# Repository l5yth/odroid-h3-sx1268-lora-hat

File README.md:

# odroid-h3-sx1268-lora-hat

Kicad files for an ODROID H3/H3+ to Raspberry-Pi pin header translator to be used with the Waveshare SX1268 LoRa hat.

* Discussion: [forum.odroid.com/topic/50464](https://forum.odroid.com/viewtopic.php?f=171&t=50464&p=400427)
* Waveshare SX1268 LoRa schematics: [files.waveshare.com/SX1268_LoRa_HAT_SchDoc.pdf](https://files.waveshare.com/upload/a/af/SX1268_LoRa_HAT_SchDoc.pdf)
* ODROID H3 schematics: [wiki.odroid.com/odroid-h3/odroid-h3_rev2.0_20220406.pdf](https://wiki.odroid.com/_media/odroid-h3/odroid-h3_rev2.0_20220406.pdf)

## LICENSE

CC0 - public domain

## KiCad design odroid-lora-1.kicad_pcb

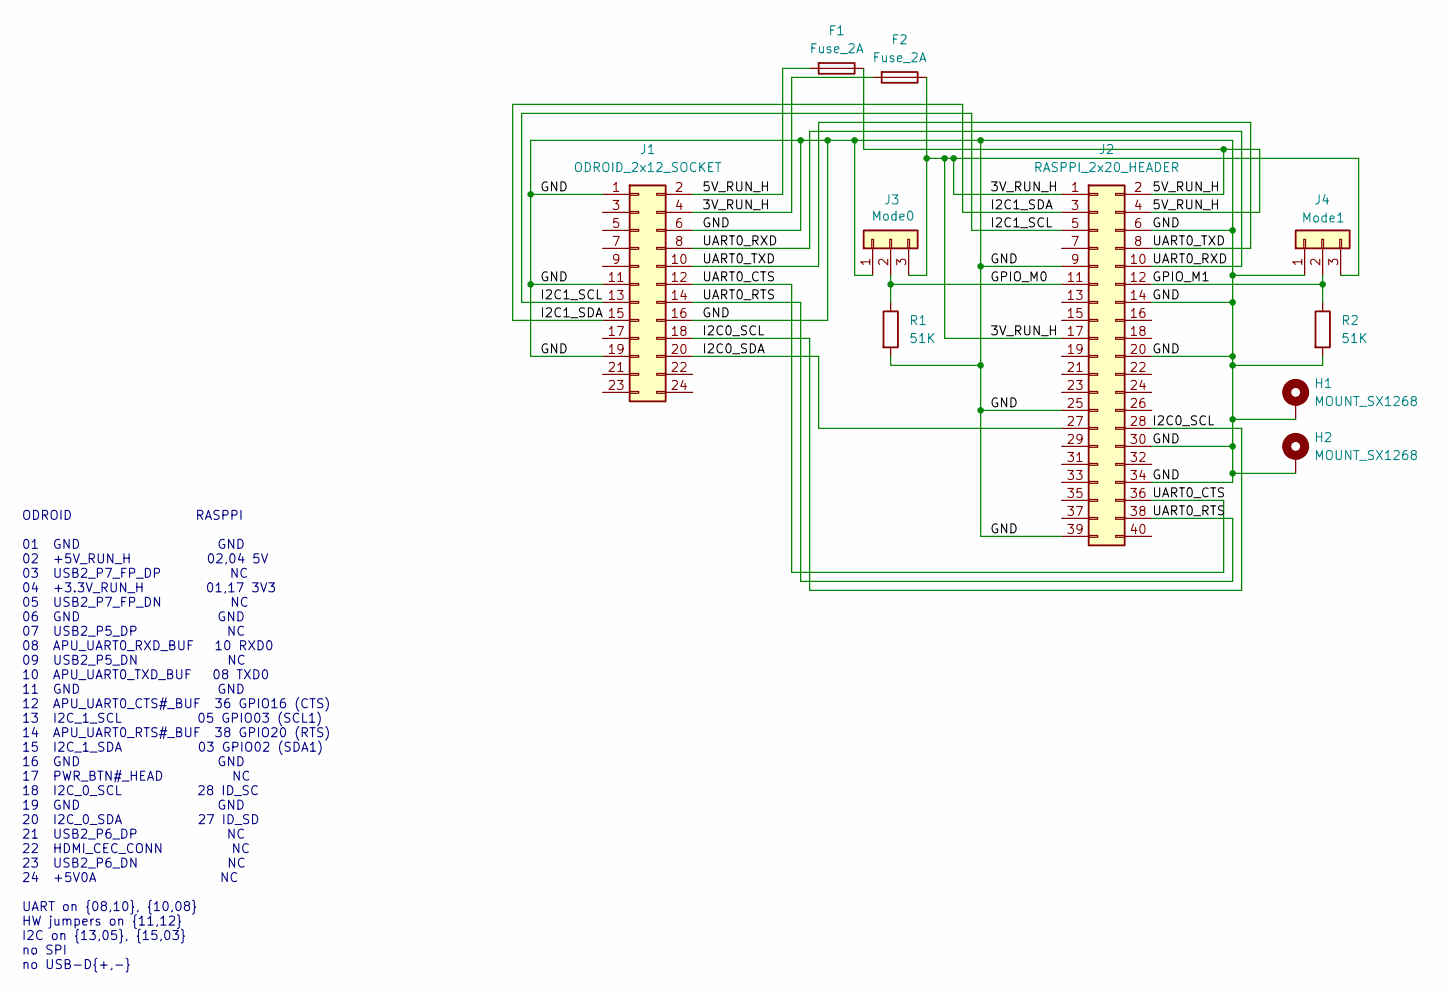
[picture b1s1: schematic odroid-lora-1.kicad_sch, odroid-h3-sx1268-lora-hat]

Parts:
F1, F2: Fuse_2A; Fuse_1206_3216Metric
H1, H2: MOUNT_SX1268; MountingHole_3.5mm_Pad
J1: ODROID_2x12_SOCKET; PinSocket_2x12_P2.54mm_Horizontal
J2: RASPPI_2x20_HEADER; PinHeader_2x20_P2.54mm_Vertical
J3: Mode0; PinHeader_1x03_P2.54mm_Vertical
J4: Mode1; PinHeader_1x03_P2.54mm_Vertical
R1, R2: 51K; R_1206_3216Metric

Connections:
/3V_RUN_H: F2.1, F2.2, J1.4, J2.1, J2.17, J3.3, J4.3
/5V_RUN_H: F1.1, F1.2, J1.2, J2.2, J2.4
/GND: H1.1, H2.1, J1.1, J1.6, J1.11, J1.16, J1.19, J2.6, J2.9, J2.14, J2.20, J2.25, J2.30, J2.34, J2.39, J3.1, J4.1, R1.2, R2.2
/GPIO_M0: J2.11, J3.2, R1.1
/GPIO_M1: J2.12, J4.2, R2.1
/I2C0_SCL: J1.18, J2.28
/I2C0_SDA: J1.20, J2.27
/I2C1_SCL: J1.13, J2.5
/I2C1_SDA: J1.15, J2.3
/UART0_CTS: J1.12, J2.36
/UART0_RTS: J1.14, J2.38
/UART0_RXD: J1.8, J2.10
/UART0_TXD: J1.10, J2.8

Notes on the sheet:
ODROID RASPPI 01 GND GND 02 +5V_RUN_H 02,04 5V 03 USB2_P7_FP_DP NC 04 +3.3V_RUN_H 01,17 3V3 05 USB2_P7_FP_DN NC 06 GND GND 07 USB2_P5_DP NC 08 APU_UART0_RXD_BUF 10 RXD0 09 USB2_P5_DN NC 10 APU_UART0_TXD_BUF 08 TXD0 11 GND GND 12 APU_UART0_CTS#_BUF 36 GPIO16 (CTS) 13 I2C_1_SCL 05 GPIO03 (SCL1) 14 AP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

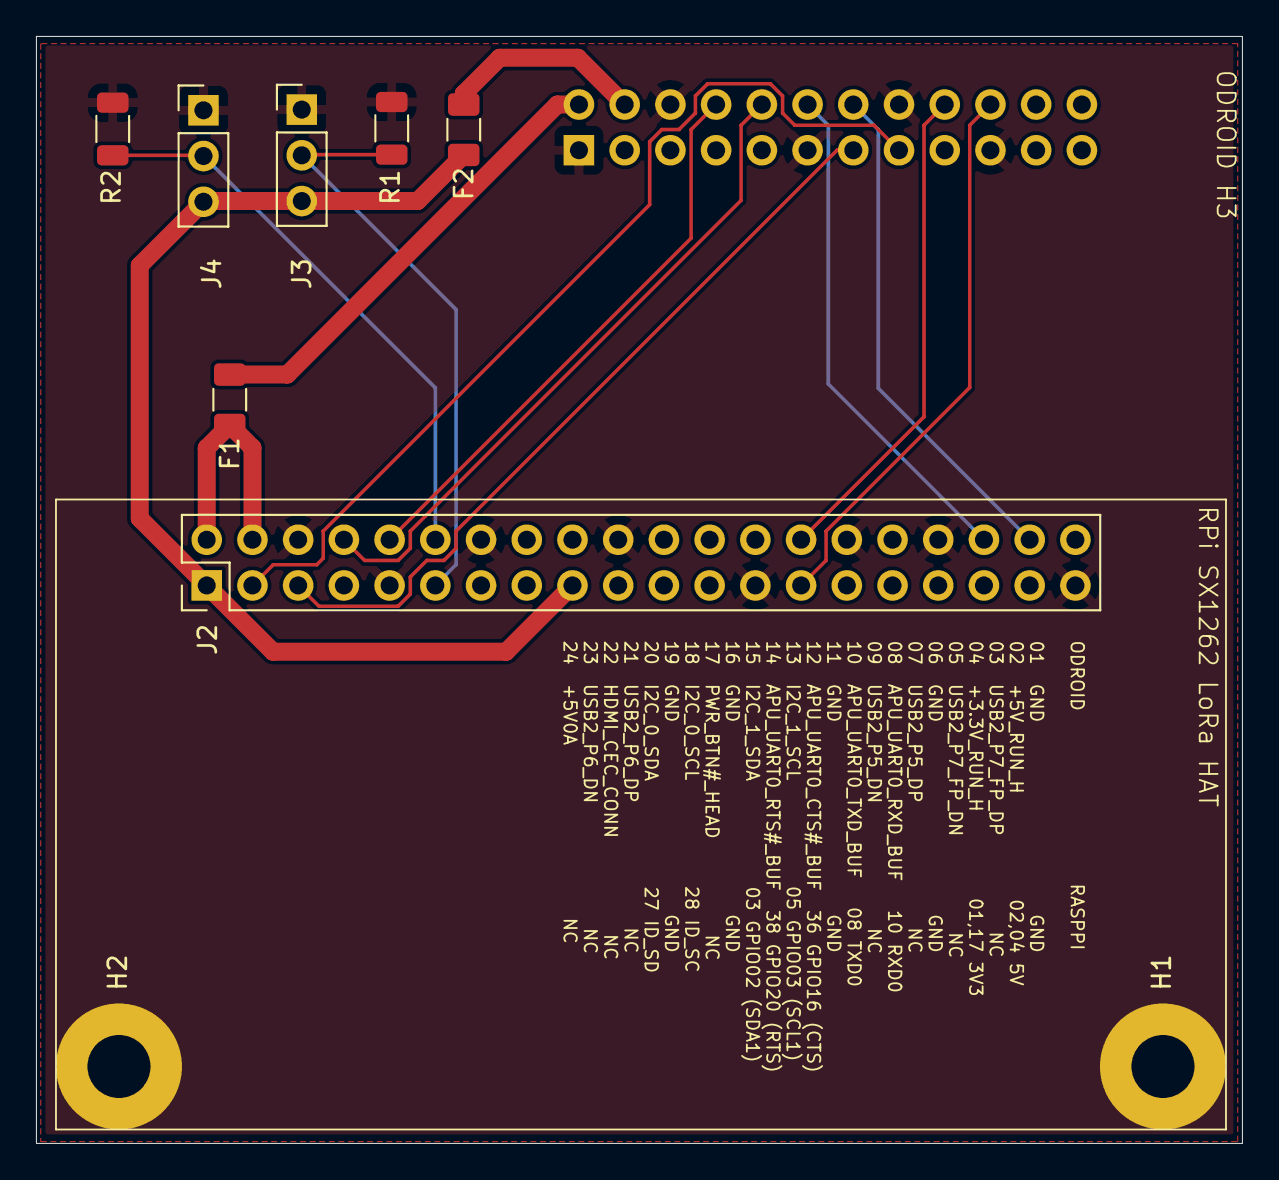
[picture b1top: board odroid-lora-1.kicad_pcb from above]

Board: 2 copper layers, 67.0 x 61.5 mm, 10 parts (1 on the bottom side), 13 nets.

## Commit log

2025-09-27 add sx1268 lora hat for odroid kicad files
2025-09-27 Select LICENSE to be CC0
2025-09-27 rename project files
2025-09-27 update to angled condensed design
2025-09-27 add screenshots
2025-09-28 replace pinheader with pinsocket for the odroid connector
2025-09-28 clean up screenshorts
2025-09-29 define power nets and increase trace width for currents
2025-10-01 add fuses
